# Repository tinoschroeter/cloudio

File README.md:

## Cloudio dein IoT Office buddy

Cloudio ueberwacht die Temperatur und Luftqualitaet. 
laesst sich mit Prometheus ansprechen um Grafana Metriken zu bekommen.

Und wenn es ganz schlimm wird, geht eine Slack Benachrichtigung raus.

[work in progress]

https://github.com/ozhantr/DigitLedDisplay

* Firebase 
  * Functions
  * Realtime Database 
  * Hosting
  * Authentication
* Prometheus
* Grafana
* Arduino
* ESP8266
* NodeJs
* JavaScript
* p5.js

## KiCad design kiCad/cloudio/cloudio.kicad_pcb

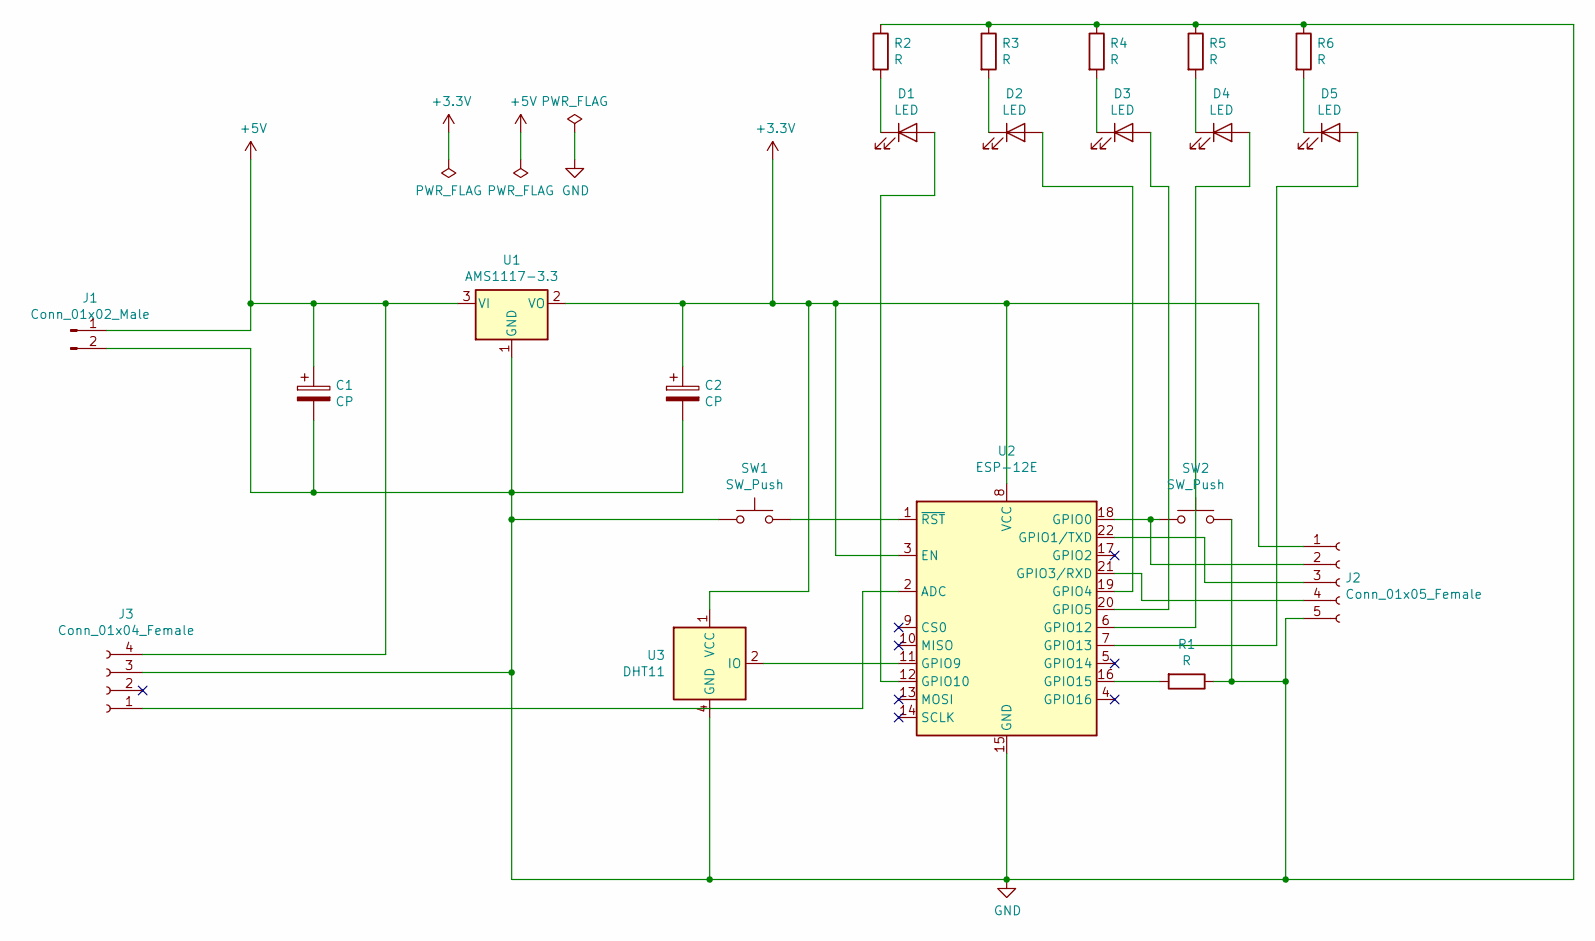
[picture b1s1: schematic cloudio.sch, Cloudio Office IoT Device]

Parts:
C1, C2: CP; CP_Radial_D4.0mm_P2.00mm
D1, D2, D3, D4, D5: LED; LED_Rectangular_W5.0mm_H2.0mm
J1: Conn_01x02_Male; PinHeader_1x02_P1.27mm_Vertical
J2: Conn_01x05_Female; PinHeader_1x05_P1.27mm_Vertical
J3: Conn_01x04_Female; PinHeader_1x04_P1.27mm_Vertical
R1, R2, R3, R4, R5, R6: R; R_0805_2012Metric_Pad1.15x1.40mm_HandSolder
SW1, SW2: SW_Push; SW_Push_1P1T_NO_CK_KSC7xxJ
U1: AMS1117-3.3; SOT-223-3_TabPin2
U2: ESP-12E
U3: DHT11; Aosong_DHT11_5.5x12.0_P2.54mm

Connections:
+3V3: C2.1, J2.1, U1.2 (VO), U2.3 (EN), U2.8 (VCC), U3.1 (VCC)
+5V: C1.1, J1.1, J3.4, U1.3 (VI)
GND: C1.2, C2.2, J1.2, J2.5, J3.3, R1.1, R2.1, R3.1, R4.1, R5.1, R6.1, SW1.1, SW2.2, U1.1 (GND), U2.15 (GND), U3.4 (GND)
unnamed: D1.1 (K), R2.2
unnamed: D1.2 (A), U2.12 (GPIO10)
unnamed: D2.1 (K), R3.2
unnamed: D2.2 (A), U2.19 (GPIO4)
unnamed: D3.1 (K), R4.2
unnamed: D3.2 (A), U2.20 (GPIO5)
unnamed: D4.1 (K), R5.2
unnamed: D4.2 (A), U2.6 (GPIO12)
unnamed: D5.1 (K), R6.2
unnamed: D5.2 (A), U2.7 (GPIO13)
unnamed: J2.2, SW2.1, U2.18 (GPIO0)
unnamed: J2.3, U2.22 (GPIO1/TXD)
unnamed: J2.4, U2.21 (GPIO3/RXD)
unnamed: J3.1, U2.2 (ADC)
unnamed: R1.2, U2.16 (GPIO15)
unnamed: SW1.2, U2.1 (~RST)
unnamed: U2.11 (GPIO9), U3.2 (IO)

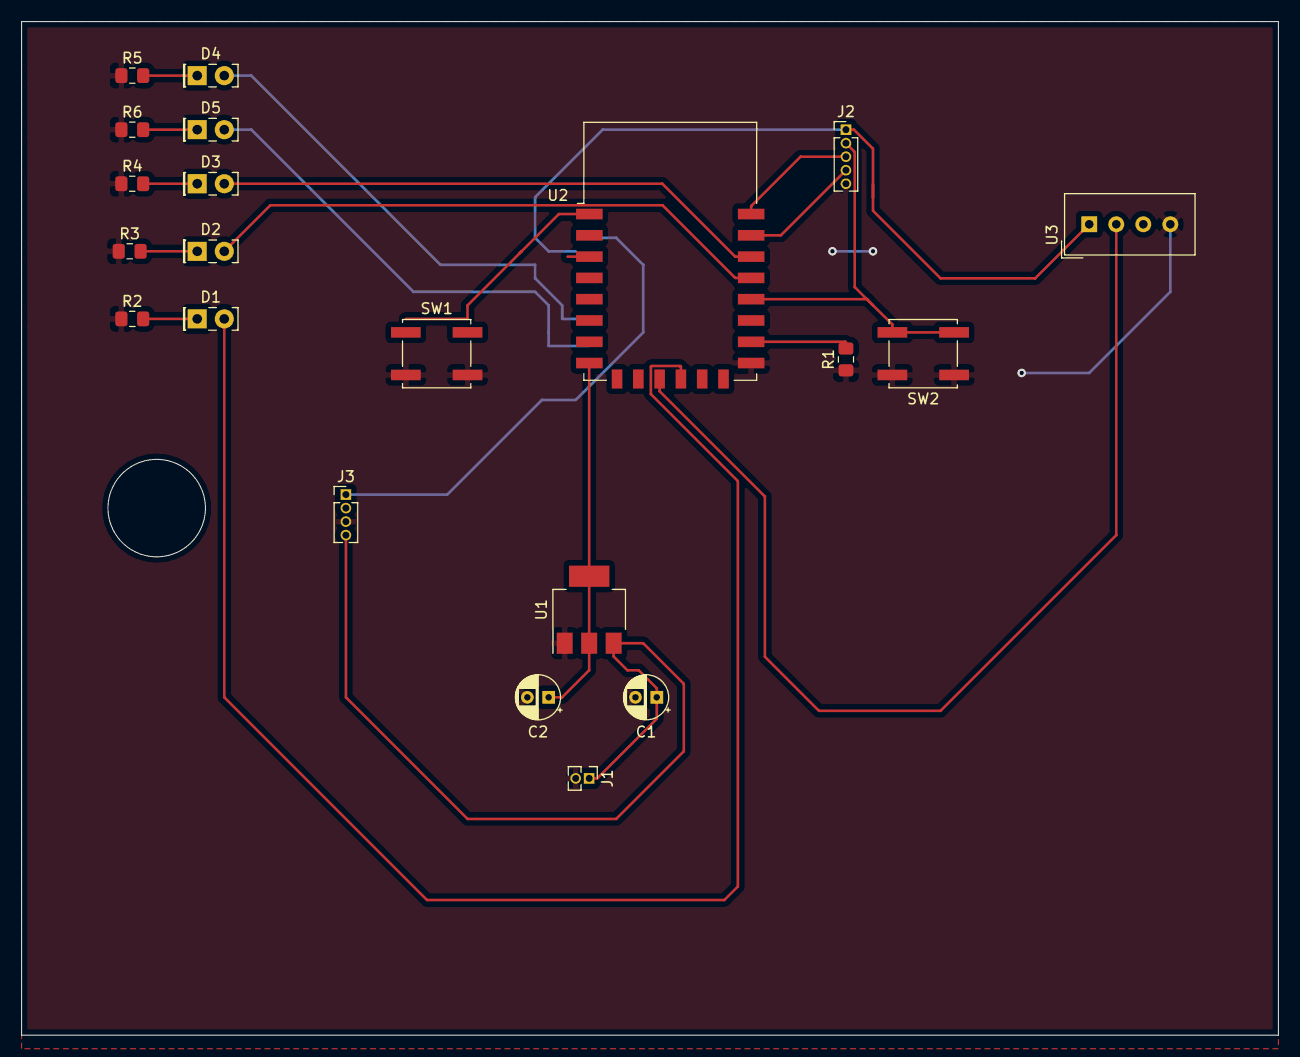
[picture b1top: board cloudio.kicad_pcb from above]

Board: 2 copper layers, 118.1 x 95.2 mm, 21 parts (0 on the bottom side), 20 nets.

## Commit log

2020-05-19 Bump acorn from 6.4.0 to 6.4.1 in /functions
    Bumps [acorn](https://github.com/acornjs/acorn) from 6.4.0 to 6.4.1.
    - [Release notes](https://github.com/acornjs/acorn/releases)
    - [Commits](https://github.com/acornjs/acorn/compare/6.4.0...6.4.1)
2020-06-08 Bump websocket-extensions from 0.1.3 to 0.1.4 in /functions
    Bumps [websocket-extensions](https://github.com/faye/websocket-extensions-node) from 0.1.3 to 0.1.4.
    - [Release notes](https://github.com/faye/websocket-extensions-node/releases)
    - [Changelog](https://github.com/faye/websocket-extensions-node/blob/master/CHANGELOG.md)
    - [Commits](https://github.com/faye/websocket-extensions-node/compare/0.1.3...0.1.4)
2020-07-20 Bump lodash from 4.17.15 to 4.17.19 in /functions
    Bumps [lodash](https://github.com/lodash/lodash) from 4.17.15 to 4.17.19.
    - [Release notes](https://github.com/lodash/lodash/releases)
    - [Commits](https://github.com/lodash/lodash/compare/4.17.15...4.17.19)
2020-09-12 Bump node-fetch from 2.6.0 to 2.6.1 in /functions
    Bumps [node-fetch](https://github.com/bitinn/node-fetch) from 2.6.0 to 2.6.1.
    - [Release notes](https://github.com/bitinn/node-fetch/releases)
    - [Changelog](https://github.com/node-fetch/node-fetch/blob/master/docs/CHANGELOG.md)
    - [Commits](https://github.com/bitinn/node-fetch/compare/v2.6.0...v2.6.1)
2021-01-06 Bump axios from 0.19.2 to 0.21.1 in /functions
    Bumps [axios](https://github.com/axios/axios) from 0.19.2 to 0.21.1.
    - [Release notes](https://github.com/axios/axios/releases)
    - [Changelog](https://github.com/axios/axios/blob/v0.21.1/CHANGELOG.md)
    - [Commits](https://github.com/axios/axios/compare/v0.19.2...v0.21.1)
2021-05-11 Bump lodash from 4.17.15 to 4.17.21 in /functions
    Bumps [lodash](https://github.com/lodash/lodash) from 4.17.15 to 4.17.21.
    - [Release notes](https://github.com/lodash/lodash/releases)
    - [Commits](https://github.com/lodash/lodash/compare/4.17.15...4.17.21)
